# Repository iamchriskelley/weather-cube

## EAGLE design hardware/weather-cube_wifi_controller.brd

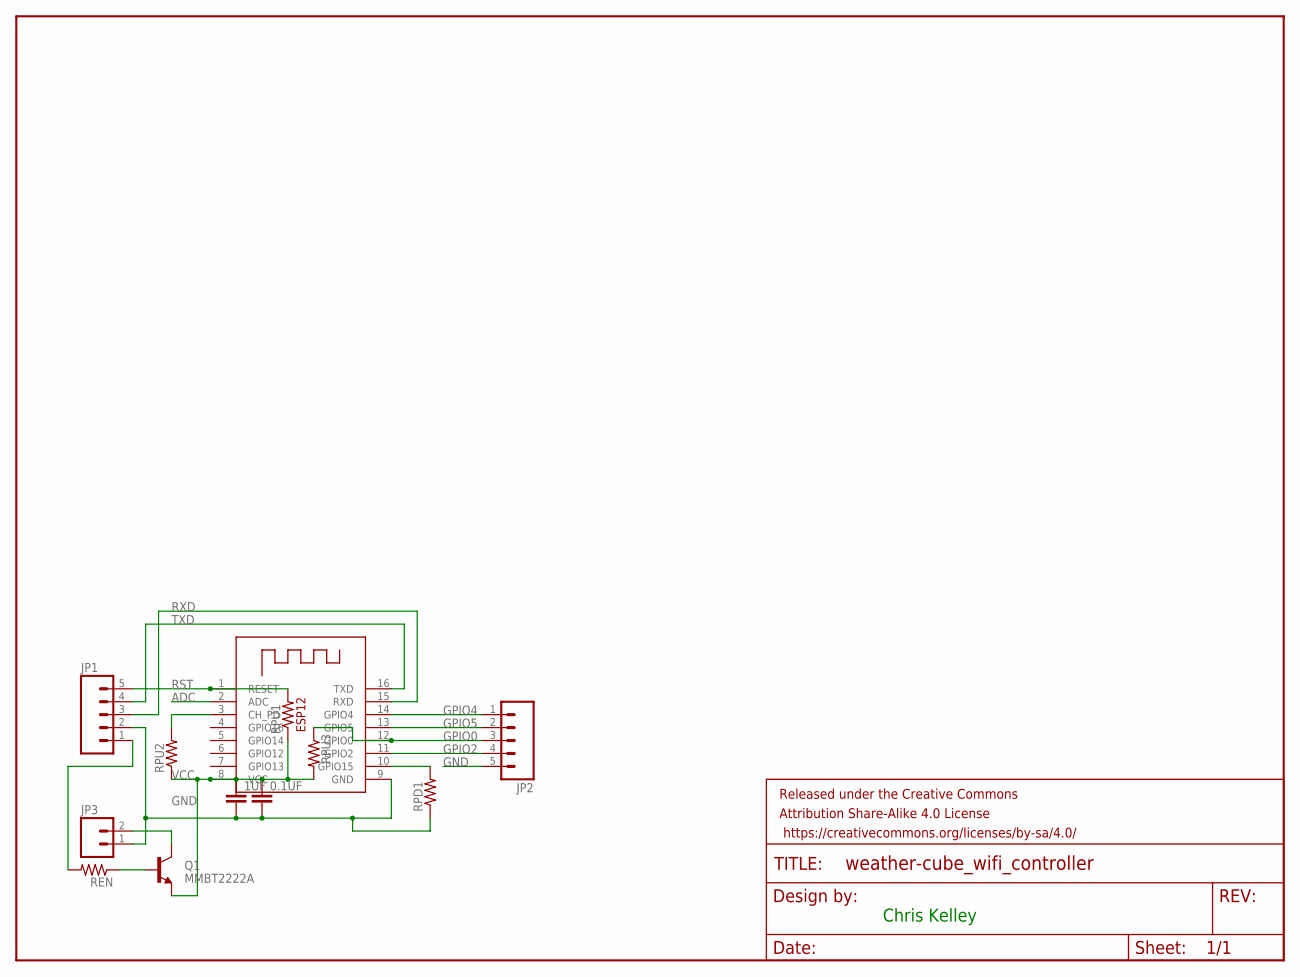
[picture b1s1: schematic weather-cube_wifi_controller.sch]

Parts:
0.1UF, 1UF: CAP0603-CAP; 0603-CAP
FRAME1: FRAME-LETTER; CREATIVE_COMMONS
JP1, JP2: M05PTH; 1X05
JP3: M02PTH; 1X02
Q1: MMBT2222A; SOT23-3
REN: RESISTOR0603-RES; 0603-RES
RPD1: RESISTOR0603-RES; 0603-RES
RPU1, RPU2, RPU3: RESISTOR0603-RES; 0603-RES
X1: ESP-12

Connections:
ADC: X1.2 (ADC)
CH_PD: RPU2.2, X1.3 (CH_PD)
GND: 0.1UF.2, 1UF.2, JP1.2, JP2.5, JP3.1, RPD1.1, X1.9 (GND)
GPIO0: JP2.3, RPU3.1, X1.12 (GPIO0)
GPIO2: JP2.4, X1.11 (GPIO2)
GPIO4: JP2.1, X1.14 (GPIO4)
GPIO5: JP2.2, X1.13 (GPIO5)
GPIO15: RPD1.2, X1.10 (GPIO15)
unnamed: JP1.1, REN.2
unnamed: Q1.1 (B), REN.1
RST: JP1.5, RPU1.2, X1.1 (RESET)
RXD: JP1.3, X1.15 (RXD)
TXD: JP1.4, X1.16 (TXD)
VCC: 0.1UF.1, 1UF.1, Q1.2 (E), RPU1.1, RPU2.1, RPU3.2, X1.8 (VCC)
VEXT: JP3.2, Q1.3 (C)

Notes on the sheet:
Chris Kelley

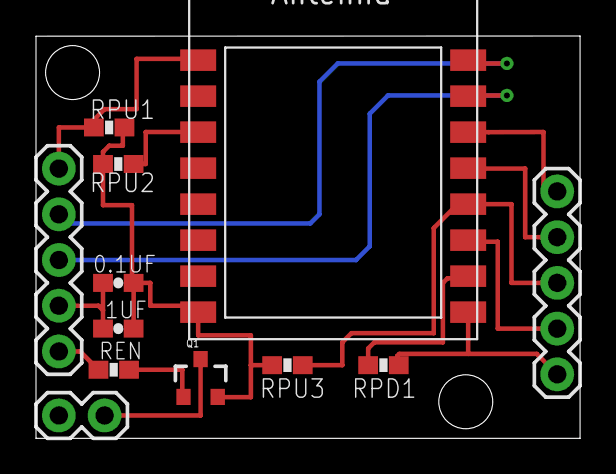
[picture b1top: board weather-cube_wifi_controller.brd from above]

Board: 2 copper layers, 30.2 x 22.4 mm, 13 parts (0 on the bottom side), 14 nets.

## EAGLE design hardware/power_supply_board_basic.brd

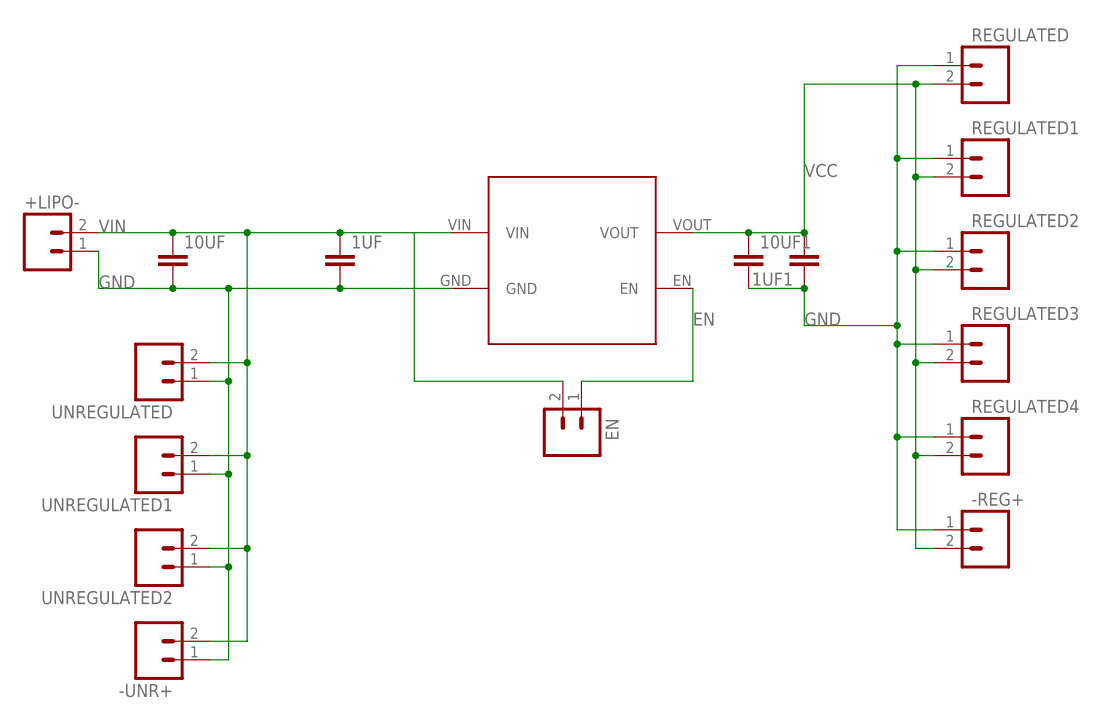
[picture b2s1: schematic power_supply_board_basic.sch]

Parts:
1UF, 1UF1, 10UF, 10UF1: CAP0603-CAP; 0603-CAP
+LIPO-: M02PTH; 1X02
-REG+: M02PTH; 1X02
-UNR+: M02PTH; 1X02
EN: M02PTH; 1X02
REGULATED, REGULATED1, REGULATED2, REGULATED3, REGULATED4: M02PTH; 1X02
U$2: AP2112K; AP2112K-SOT23-5
UNREGULATED, UNREGULATED1, UNREGULATED2: M02PTH; 1X02

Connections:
EN: EN.1, U$2.EN
GND: 1UF.2, 1UF1.1, 10UF.2, 10UF1.2, +LIPO-.1, -REG+.1, -UNR+.1, REGULATED.1, REGULATED1.1, REGULATED2.1, REGULATED3.1, REGULATED4.1, U$2.GND, UNREGULATED.1, UNREGULATED1.1, UNREGULATED2.1
VCC: 1UF1.2, 10UF1.1, -REG+.2, REGULATED.2, REGULATED1.2, REGULATED2.2, REGULATED3.2, REGULATED4.2, U$2.VOUT
VIN: 1UF.1, 10UF.1, +LIPO-.2, -UNR+.2, EN.2, U$2.VIN, UNREGULATED.2, UNREGULATED1.2, UNREGULATED2.2

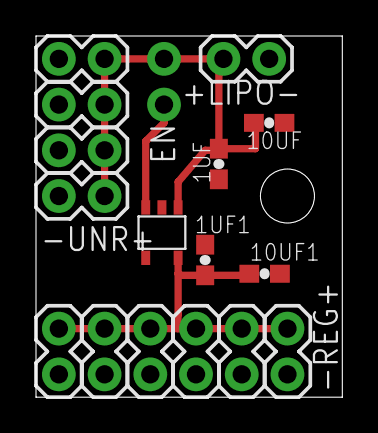
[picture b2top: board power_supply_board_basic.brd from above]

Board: 2 copper layers, 17.0 x 20.1 mm, 17 parts (1 on the bottom side), 4 nets.

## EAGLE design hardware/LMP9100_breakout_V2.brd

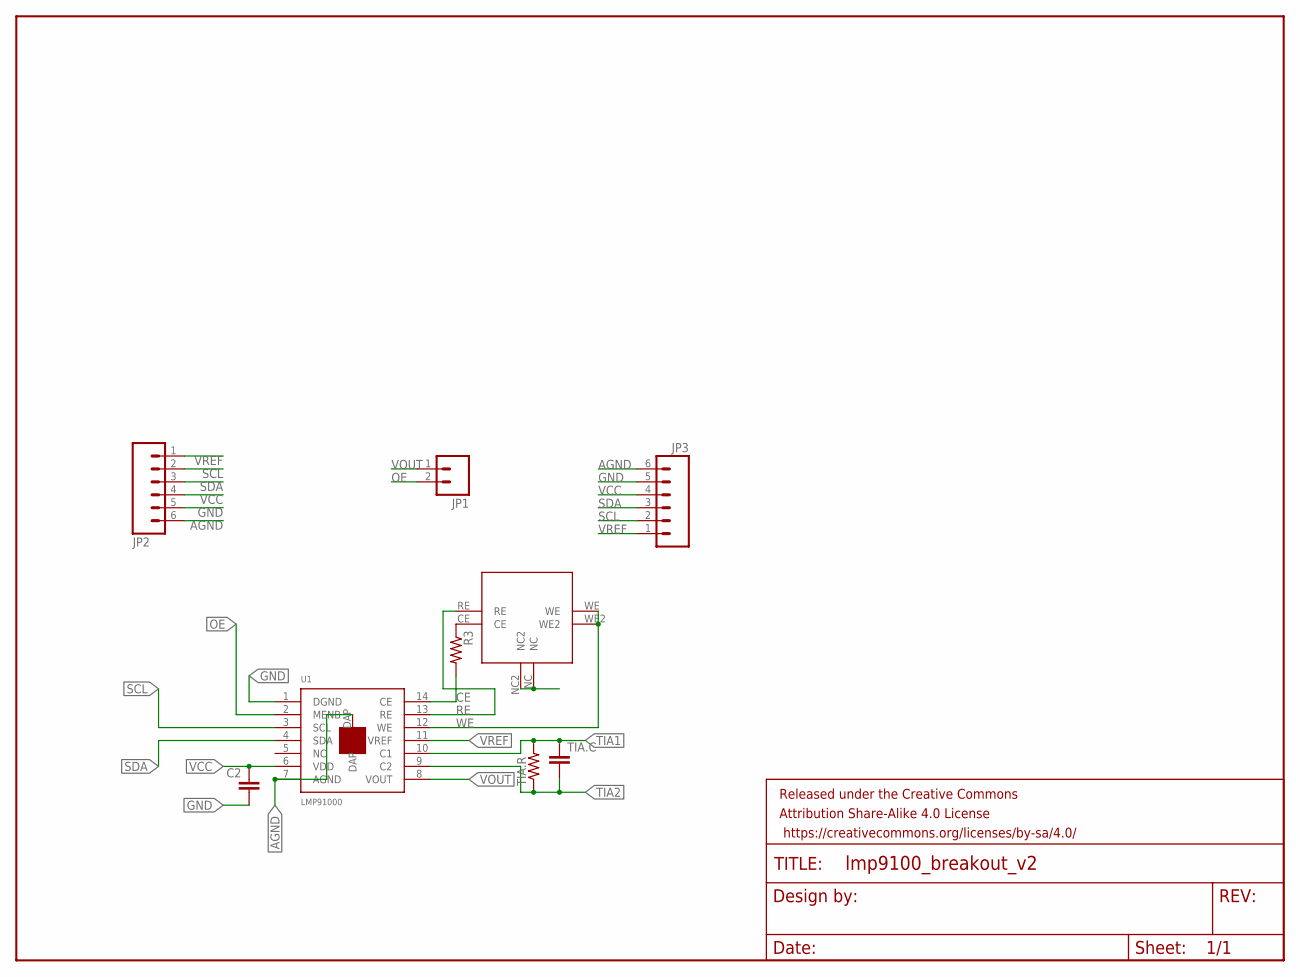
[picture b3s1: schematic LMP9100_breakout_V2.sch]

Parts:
C2: CAP0603-CAP; 0603-CAP
FRAME1: FRAME-LETTER; CREATIVE_COMMONS
JP1: M02PTH; 1X02
JP2, JP3: M06SILK_FEMALE_PTH; 1X06
R3: RESISTOR0603-RES; 0603-RES
TIA.C: CAP0603-CAP; 0603-CAP
TIA.R: RESISTOR0603-RES; 0603-RES
U1: LMP91000
U$1: SPEC-SENSOR

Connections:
AGND: JP2.6, JP3.6, U1.7 (AGND), U1.DAP
CE: R3.2, U1.14 (CE)
GND: C2.2, JP2.5, JP3.5, U1.1 (DGND), U$1.NC, U$1.NC2
unnamed: R3.1, U$1.CE
OE: JP1.2, U1.2 (MENB)
RE: U1.13 (RE), U$1.RE
SCL: JP2.2, JP3.2, U1.3 (SCL)
SDA: JP2.3, JP3.3, U1.4 (SDA)
TIA1: TIA.C.1, TIA.R.2, U1.10 (C1)
TIA2: TIA.C.2, TIA.R.1, U1.9 (C2)
VCC: C2.1, JP2.4, JP3.4, U1.6 (VDD)
VOUT: JP1.1, U1.8 (VOUT)
VREF: JP2.1, JP3.1, U1.11 (VREF)
WE: U1.12 (WE), U$1.WE, U$1.WE2

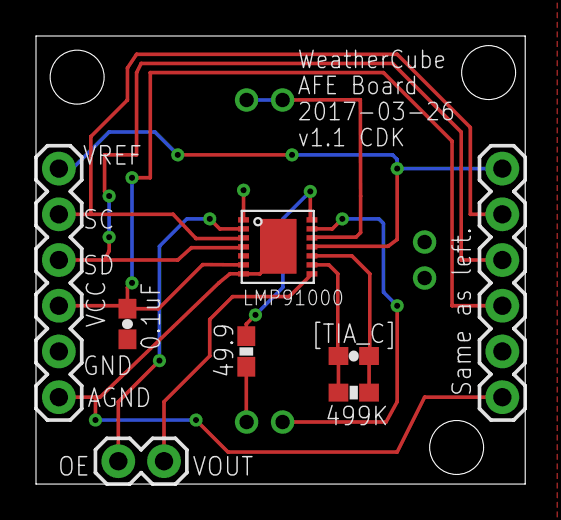
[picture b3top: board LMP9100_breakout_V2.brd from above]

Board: 2 copper layers, 27.2 x 24.9 mm, 10 parts (0 on the bottom side), 14 nets.

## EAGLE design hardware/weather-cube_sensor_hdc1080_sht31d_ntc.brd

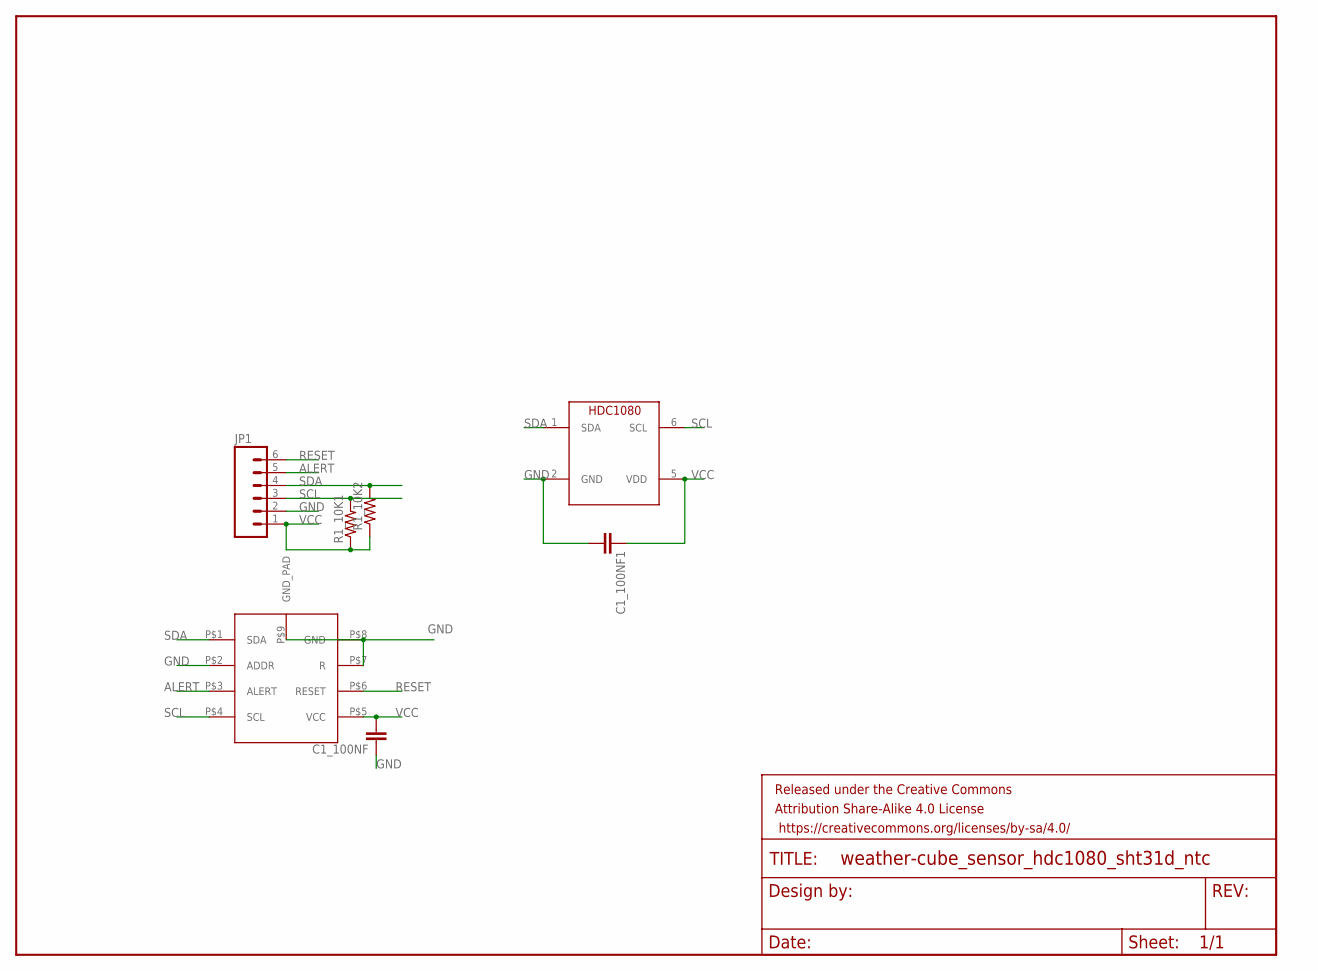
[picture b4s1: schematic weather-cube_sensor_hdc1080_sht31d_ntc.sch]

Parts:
C1_100NF, C1_100NF1: CAP0603-CAP; 0603-CAP
FRAME1: FRAME-LETTER; CREATIVE_COMMONS
JP1: M06SILK_FEMALE_PTH; 1X06
R1_10K1, R1_10K2: RESISTOR0603-RES; 0603-RES
U$1: SHT31-D
U$2: HDC1080; WSON-6-PAD

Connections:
ALERT: JP1.5, U$1.P$3 (ALERT)
GND: C1_100NF.1, C1_100NF1.2, JP1.2, U$1.P$2 (ADDR), U$1.P$7 (R), U$1.P$8 (GND), U$1.P$9 (GND_PAD), U$2.2 (GND)
RESET: JP1.6, U$1.P$6 (RESET)
SCL: JP1.3, R1_10K1.2, U$1.P$4 (SCL), U$2.6 (SCL)
SDA: JP1.4, R1_10K2.2, U$1.P$1 (SDA), U$2.1 (SDA)
VCC: C1_100NF.2, C1_100NF1.1, JP1.1, R1_10K1.1, R1_10K2.1, U$1.P$5 (VCC), U$2.5 (VDD)

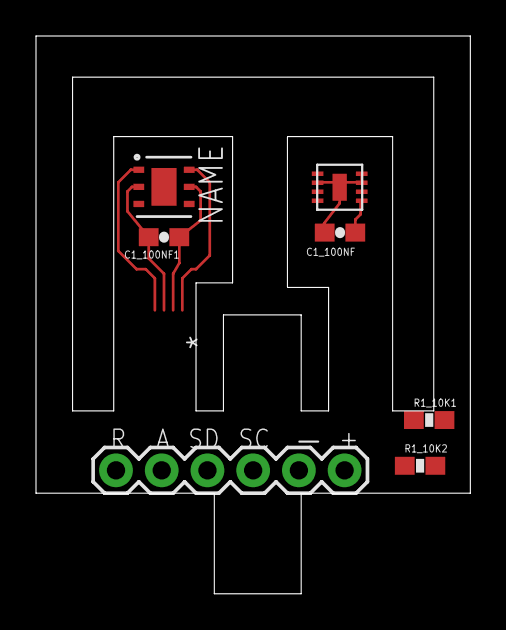
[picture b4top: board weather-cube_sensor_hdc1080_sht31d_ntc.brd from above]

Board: 2 copper layers, 24.1 x 31.0 mm, 8 parts (0 on the bottom side), 6 nets.

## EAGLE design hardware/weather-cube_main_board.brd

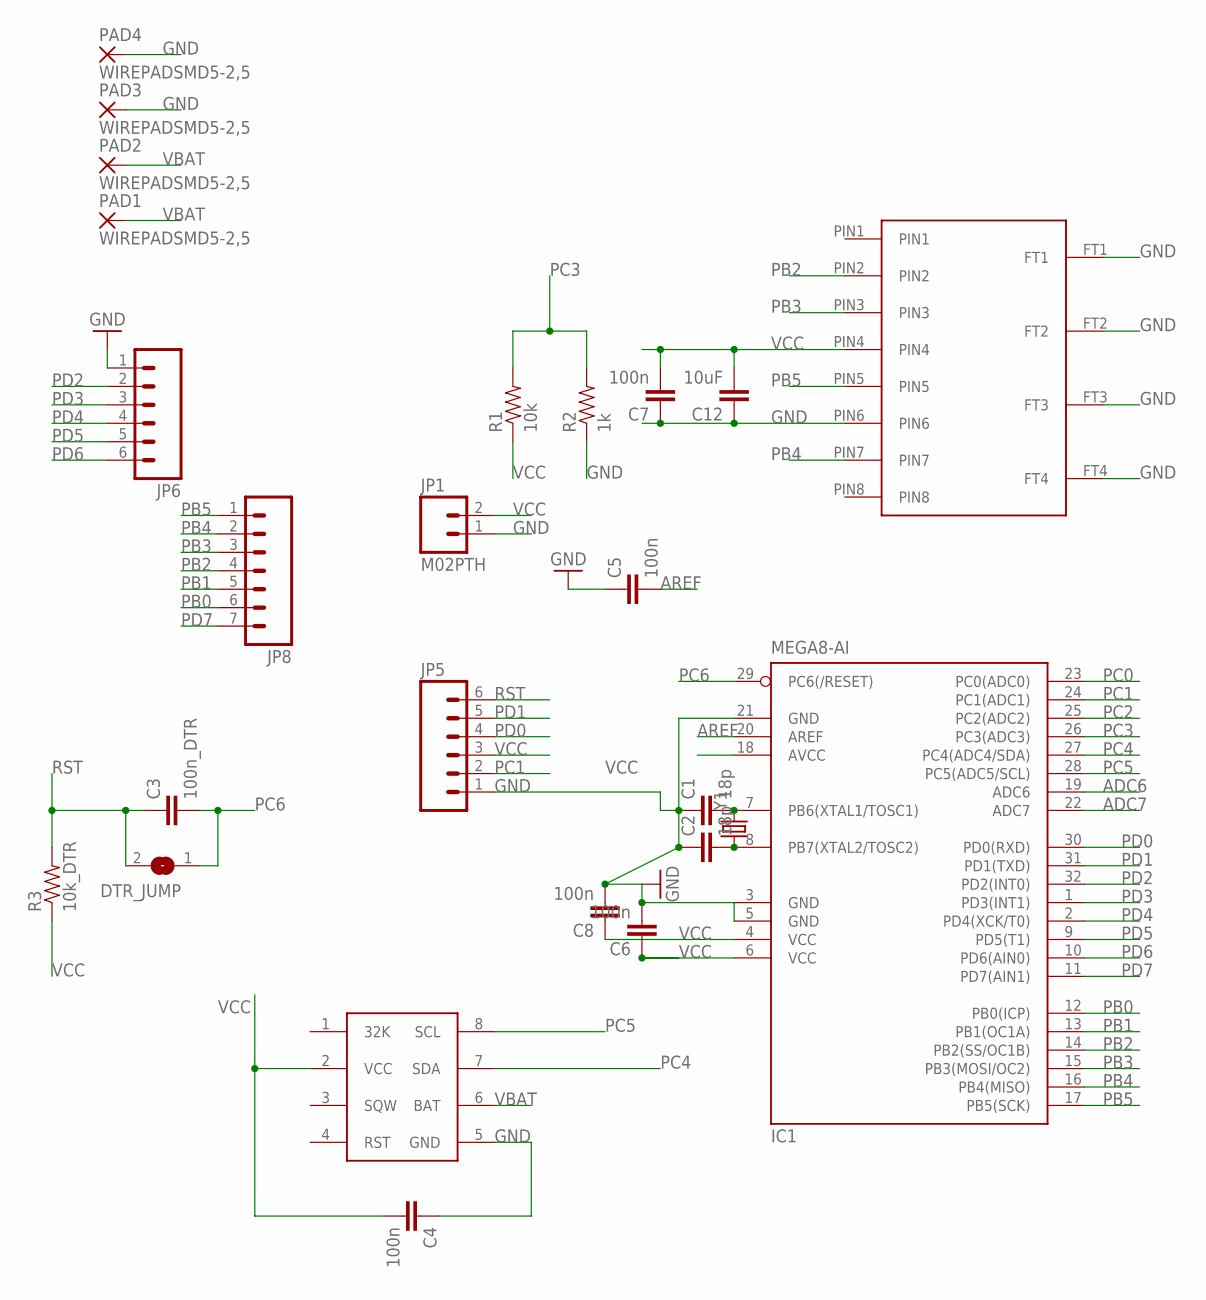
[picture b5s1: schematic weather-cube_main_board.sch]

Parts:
*RTC: DS3231M
C1, C2: 18p; 0603-CAP
C3: 100n_DTR; 0603-CAP
C4, C5, C6, C7, C8: 100n; 0603-CAP
C12: 10uF; 0603-CAP
DTR_JUMP: SJ
IC1: MEGA8-AI; TQFP32-08
JP1: M02PTH; 1X02
JP5, JP6: M06SIP; 1X06
JP8: M07; 1X07
MICRO-SD: MICROSD-1010030368
PAD1, PAD2, PAD3, PAD4: WIREPADSMD5-2,5; 5-2,5
R1: 10k; 0603-RES
R2: 1k; 0603-RES
R3: 10k_DTR; 0603-RES
Y1: CRYSTAL5X3; CRYSTAL-SMD-5X3

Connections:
ADC6: IC1.19 (ADC6)
ADC7: IC1.22 (ADC7)
AREF: C5.2, IC1.20 (AREF)
GND: *RTC.5 (GND), C1.1, C2.1, C4.1, C5.1, C6.2, C7.1, C8.2, C12.1, IC1.3 (GND), IC1.5 (GND), IC1.21 (GND), JP1.1, JP5.1, JP6.1, MICRO-SD.FT1, MICRO-SD.FT2, MICRO-SD.FT3, MICRO-SD.FT4, MICRO-SD.PIN6, PAD3.1, PAD4.1, R2.1
PB0: IC1.12 (PB0(ICP)), JP8.6
PB1: IC1.13 (PB1(OC1A)), JP8.5
PB2: IC1.14 (PB2(SS/OC1B)), JP8.4, MICRO-SD.PIN2
PB3: IC1.15 (PB3(MOSI/OC2)), JP8.3, MICRO-SD.PIN3
PB4: IC1.16 (PB4(MISO)), JP8.2, MICRO-SD.PIN7
PB5: IC1.17 (PB5(SCK)), JP8.1, MICRO-SD.PIN5
PC0: IC1.23 (PC0(ADC0))
PC1: IC1.24 (PC1(ADC1)), JP5.2
PC2: IC1.25 (PC2(ADC2))
PC3: IC1.26 (PC3(ADC3)), R1.2, R2.2
PC4: *RTC.7 (SDA), IC1.27 (PC4(ADC4/SDA))
PC5: *RTC.8 (SCL), IC1.28 (PC5(ADC5/SCL))
PC6: C3.2, DTR_JUMP.1, IC1.29 (PC6(/RESET))
PD0: IC1.30 (PD0(RXD)), JP5.4
PD1: IC1.31 (PD1(TXD)), JP5.5
PD2: IC1.32 (PD2(INT0)), JP6.2
PD3: IC1.1 (PD3(INT1)), JP6.3
PD4: IC1.2 (PD4(XCK/T0)), JP6.4
PD5: IC1.9 (PD5(T1)), JP6.5
PD6: IC1.10 (PD6(AIN0)), JP6.6
PD7: IC1.11 (PD7(AIN1)), JP8.7
Q1: C2.2, IC1.8 (PB7(XTAL2/TOSC2)), Y1.1
Q2: C1.2, IC1.7 (PB6(XTAL1/TOSC1)), Y1.3 (2)
RST: C3.1, DTR_JUMP.2, JP5.6, R3.2
VBAT: *RTC.6 (BAT), PAD1.1, PAD2.1
VCC: *RTC.2 (VCC), C4.2, C6.1, C7.2, C8.1, C12.2, IC1.4 (VCC), IC1.6 (VCC), IC1.18 (AVCC), JP1.2, JP5.3, MICRO-SD.PIN4, R1.1, R3.1

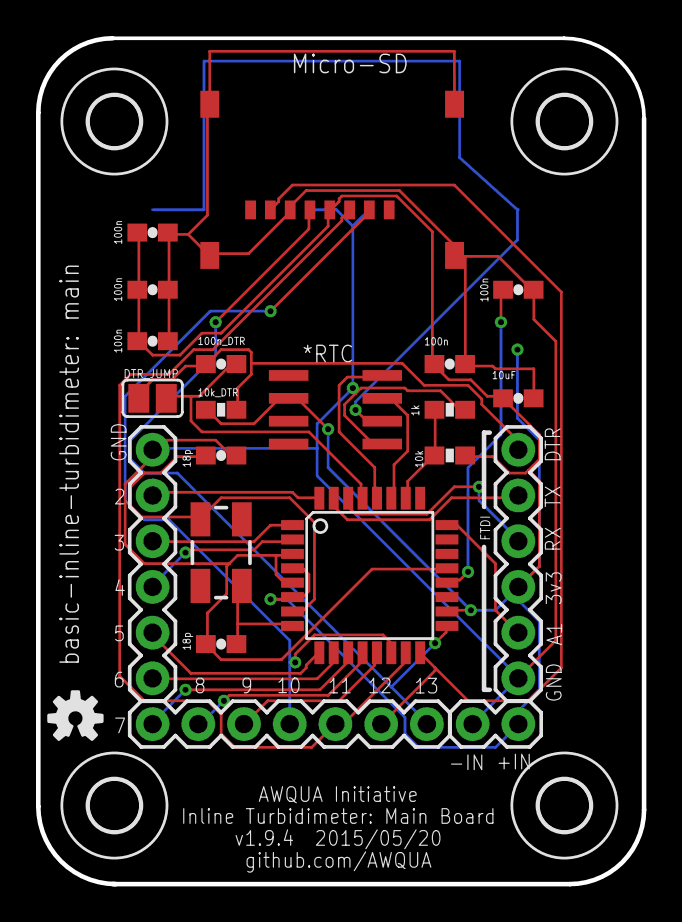
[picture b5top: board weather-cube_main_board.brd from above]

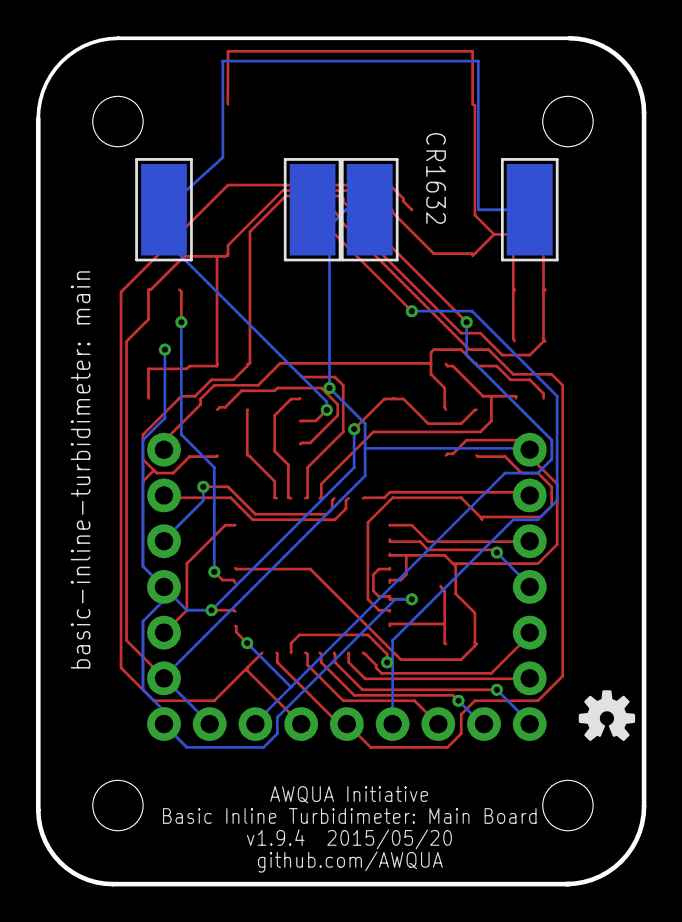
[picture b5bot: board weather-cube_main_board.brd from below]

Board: 2 copper layers, 33.7 x 47.0 mm, 31 parts (5 on the bottom side), 26 nets.

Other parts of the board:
U$1, U$3, U$5, U$6: 2,8
U$2, U$8: OSHW-LOGO-S

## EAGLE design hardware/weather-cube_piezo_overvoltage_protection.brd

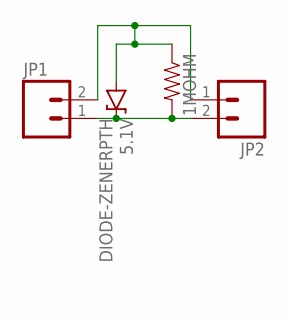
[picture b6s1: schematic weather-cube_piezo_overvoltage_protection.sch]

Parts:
1MOHM: RESISTORAXIAL-0.3; AXIAL-0.3
5.1V: DIODE-ZENERPTH; DIODE-ZENER
JP1, JP2: M02PTH; 1X02

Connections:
GND: 1MOHM.P$1 (1), 5.1V.P$2 (A), JP1.2, JP2.1
unnamed: 1MOHM.P$2 (2), 5.1V.P$1 (C), JP1.1, JP2.2

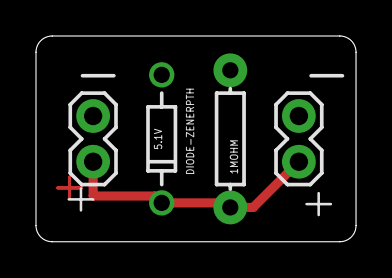
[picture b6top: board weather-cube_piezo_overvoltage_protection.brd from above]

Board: 2 copper layers, 17.8 x 11.4 mm, 4 parts (0 on the bottom side), 2 nets.

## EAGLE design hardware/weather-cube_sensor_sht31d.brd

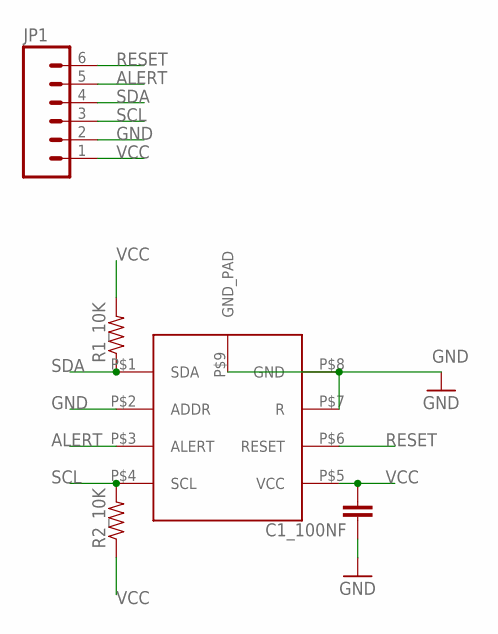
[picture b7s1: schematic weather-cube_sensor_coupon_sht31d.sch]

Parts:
C1_100NF: CAP0603-CAP; 0603-CAP
JP1: M06SILK_FEMALE_PTH; 1X06
R1_10K, R2_10K: RESISTOR0603-RES; 0603-RES
U$1: SHT31-D

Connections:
ALERT: JP1.5, U$1.P$3 (ALERT)
GND: C1_100NF.1, JP1.2, U$1.P$2 (ADDR), U$1.P$7 (R), U$1.P$8 (GND), U$1.P$9 (GND_PAD)
RESET: JP1.6, U$1.P$6 (RESET)
SCL: JP1.3, R2_10K.2, U$1.P$4 (SCL)
SDA: JP1.4, R1_10K.1, U$1.P$1 (SDA)
VCC: C1_100NF.2, JP1.1, R1_10K.2, R2_10K.1, U$1.P$5 (VCC)

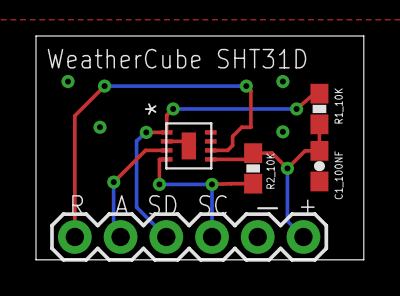
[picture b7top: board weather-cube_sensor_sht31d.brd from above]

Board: 2 copper layers, 18.2 x 12.4 mm, 5 parts (0 on the bottom side), 6 nets.

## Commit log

2017-03-21 added stencil-cutting files for sht31d
2017-03-31 incomplete sensor combo board (HDC1080, SHT31, NTC) added
2017-04-10 added power supply and wifi boards

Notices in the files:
parts and their libraries:
SparkFun-Passives: Licensing: Creative Commons ShareAlike 4.0 International - https://creativecommons.org/licenses/by-sa/4.0
SparkFun-Aesthetics: Released under the Creative Commons Attribution Share-Alike 4.0 License
SparkFun-Aesthetics: https://creativecommons.org/licenses/by-sa/4.0
